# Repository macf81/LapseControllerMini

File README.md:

# LapseControllerMini
Teensy timelapse controller

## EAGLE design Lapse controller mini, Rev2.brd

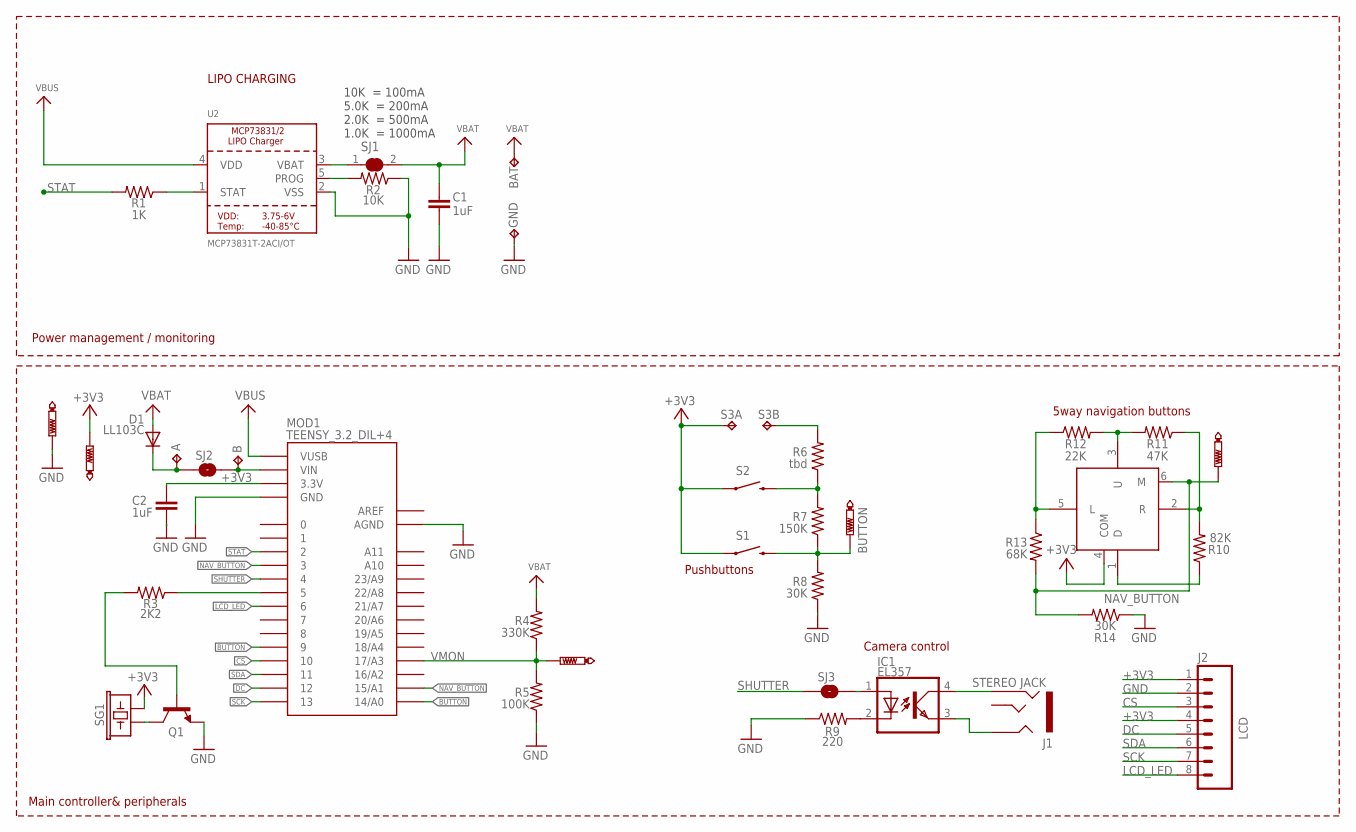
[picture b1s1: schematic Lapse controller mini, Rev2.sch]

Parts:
3V3: PTR1PAD1-13; P1-13
A: TPTP17SQ; TP17SQ
B: TPTP17SQ; TP17SQ
BAT: VBAT; P1-PAD_B
BTN: PTR1PAD1-13; P1-13
BUTTONS1: GND; P1-13
C1, C2: 1uF; C0805K
D1: LL103C; MINIMELF
GND: GND; P1-PAD_B
IC1: EL357; SOP-4
J1: STEREO JACK; AUDIO-JACK-TRRS-SMD
J2: LCD; 1X08_NO_SILK
MOD1: TEENSY_3.2_DIL+4; TEENSY3-DIL+4
Q1: TRANSISTOR_NPNSOT23-3; SOT23-3
R1: 1K; 1206
R2: 10K; 1206
R3: 2K2; 1206
R4: 330K; 1206
R5: 100K; 1206
R6: tbd; 1206
R7: 150K; 1206
R8, R14: 30K; 1206
R9: 220; 1206
R10: 82K; 1206
R11: 47K; 1206
R12: 22K; 1206
R13: 68K; 1206
S1, S2: MOMENTARY-SWITCH-SPSTTACTILE_SWITCH_PTHA; TACTILE_SWITCH_PTH
S3A, S3B: TPPAD1_B; P1-PAD_B
SG1: BUZZERSMD2; BUZZER-HCS09H
SJ1: SOLDERJUMPER_CLOSED; SOLDERJUMPER_CLOSEDWIRE
SJ2, SJ3: JUMPER-PAD-2-NO; PAD-JUMPER-2-NO_NO_SILK
SW1: MICROBUILDER_NAVSWITCH; MICROBUILDER_SKQUBAE010BB
U2: MCP73831T-2ACI/OT; SOT23-5
VM: PTR1PAD1-13; P1-13
XY: PTR1PAD1-13; P1-13

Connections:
+3V3: 3V3.TP, C2.1, J2.1, J2.4, MOD1.3.3V, S1.P$1 (1), S2.P$1 (1), S3A.TP, SG1.- (2), SW1.4 (COM)
AREF: MOD1.AREF
BUTTON: BTN.TP, MOD1.9, MOD1.14/A0, R7.1, R8.2, S1.P$2 (2)
CS: J2.3, MOD1.10
DC: J2.5, MOD1.12
GND: BUTTONS1.TP, C1.2, C2.2, GND.TP, J2.2, MOD1.AGND, MOD1.GND, Q1.2 (E), R2.1, R5.1, R8.1, R9.1, R14.1, U2.2 (VSS)
LCD_LED: J2.8, MOD1.6
unnamed: R10.1, SW1.1 (D)
unnamed: IC1.2 (C), R9.2
unnamed: A.TP, D1.C, SJ2.1
unnamed: IC1.4 (COL), J1.RING2A (RING2), J1.RING2B (RING2)
unnamed: IC1.3 (EMIT), J1.RING1A (RING1), J1.RING1B (RING1)
unnamed: R1.1, U2.1 (STAT)
unnamed: R2.2, U2.5 (PROG)
unnamed: SJ1.1, U2.3 (VBAT)
unnamed: MOD1.5, R3.1
unnamed: R10.2, R11.1, SW1.2 (R)
unnamed: R11.2, R12.2, SW1.3 (U)
unnamed: R12.1, R13.1, SW1.5 (L)
unnamed: B.TP, MOD1.VIN, SJ2.2
unnamed: R6.2, S3B.TP
unnamed: Q1.1 (B), R3.2
unnamed: Q1.3 (C), SG1.+ (1)
unnamed: R6.1, R7.2, S2.P$2 (2)
NAV_BUTTON: MOD1.3, MOD1.15/A1, R13.2, R14.2, SW1.6 (M), XY.TP
SCK: J2.7, MOD1.13
SDA: J2.6, MOD1.11
SHUTTER: MOD1.4, SJ3.1
SHUTTER_A: IC1.1 (A), SJ3.2
STAT: MOD1.2, R1.2
VBAT: BAT.TP, C1.1, D1.A, R4.2, SJ1.2
VBUS: MOD1.VUSB, U2.4 (VDD)
VMON: MOD1.17/A3, R4.1, R5.2, VM.TP

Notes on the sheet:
Power management / monitoring
Main controller& peripherals
Camera control
10K = 100mA
5.0K = 200mA
2.0K = 500mA
1.0K = 1000mA
LIPO CHARGING
Pushbuttons
5way navigation buttons

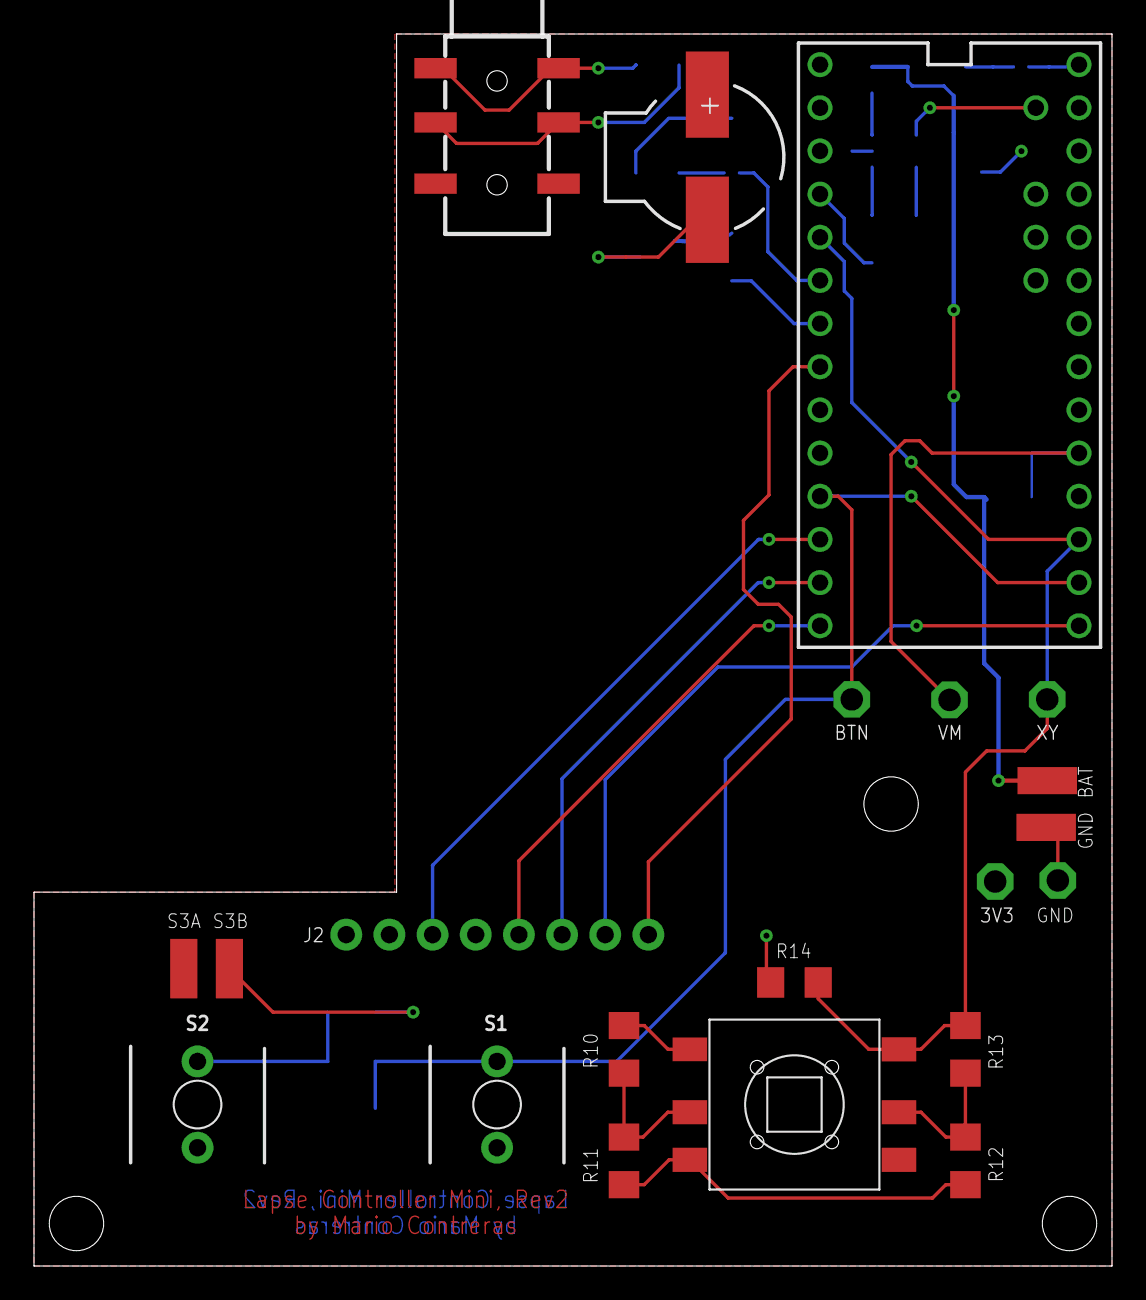
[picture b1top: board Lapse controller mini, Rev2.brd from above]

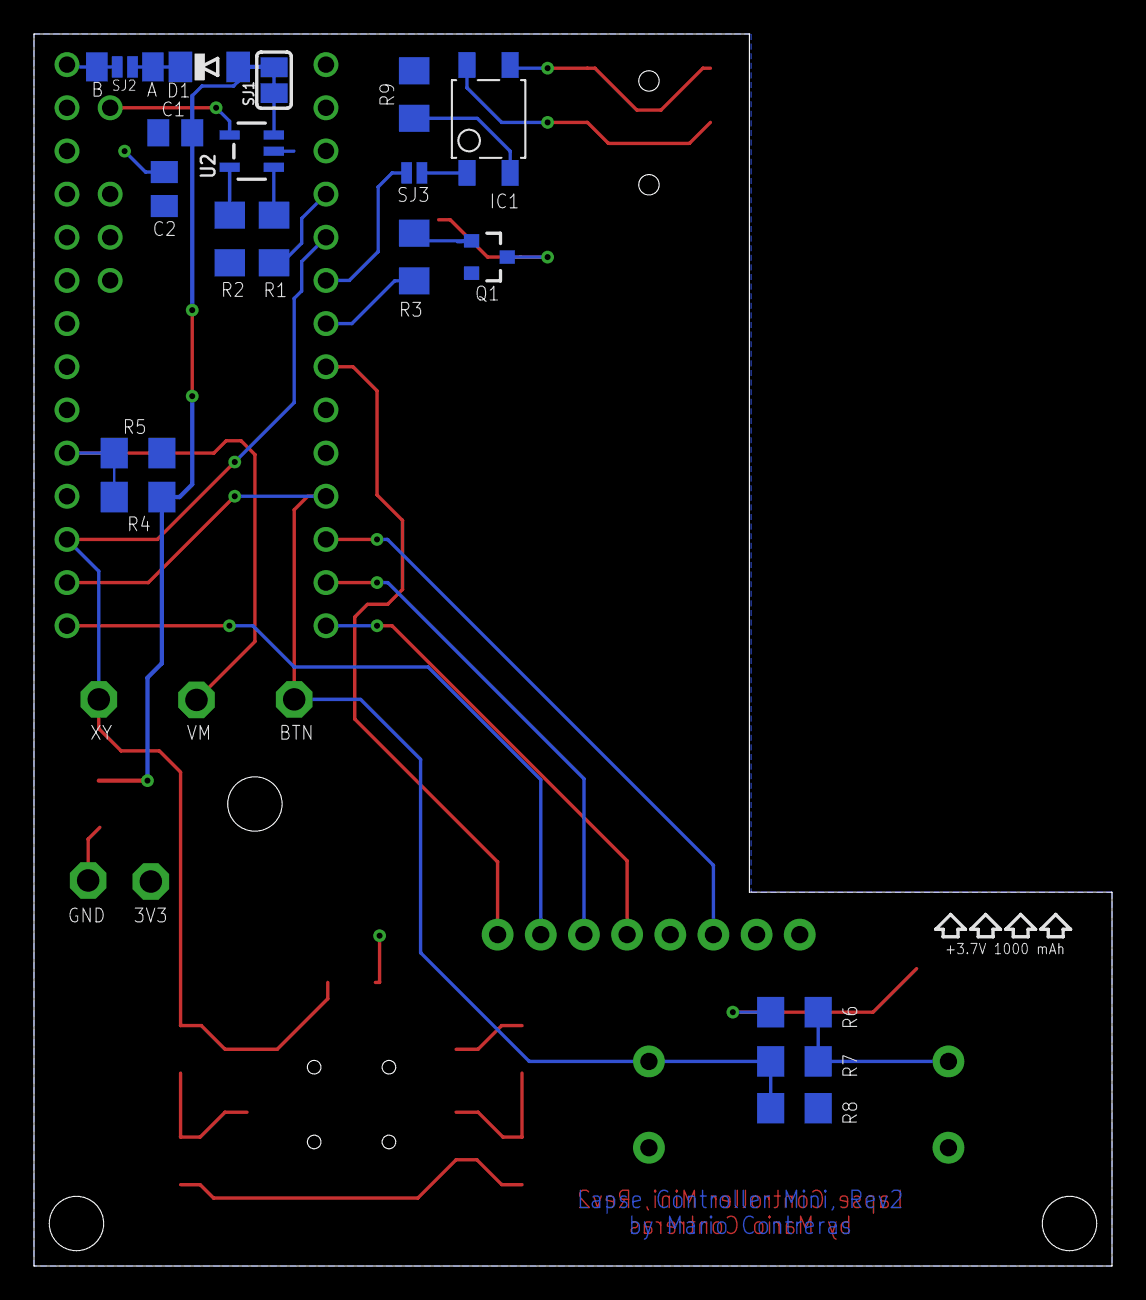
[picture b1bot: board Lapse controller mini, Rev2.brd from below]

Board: 2 copper layers, 63.4 x 72.5 mm, 41 parts (20 on the bottom side), 32 nets.

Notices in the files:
parts and their libraries:
SparkFun-Connectors: Licensing: Creative Commons ShareAlike 4.0 International - https://creativecommons.org/licenses/by-sa/4.0
microbuilder: This work is placed in the public domain, and may be freely used for commercial and non-commercial work with the following conditions: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
